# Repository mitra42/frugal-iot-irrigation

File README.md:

# Frugal-IoT Irrigation

This project is intended to provide solar-powered irrigation for small farms. A set of sectors is watered one at a time, once a day. 

The default version waters each sector until its soil reaches a target moisture or a time limit runs out, but it can be 
subclased for more complex per-sector requirements. 

There are tank-level and battery interlocks that stop the whole run, and this also can be customized. 

It is built on top of Frugal-IoT and both the irrigation and MPPT components draw part of their
inspiration from [OSPIT](https://www.apc.org/en/news/meet-ospit-sustainable-energy-and-irrigation-solution-community-networks)
(Lua on the FF-ESP32-OpenMPPT solar charge controller)
- [OSPIT_COMPARISON.md](OSPIT_COMPARISON.md) describes what is different and why.

This release should work in several hardware environments.

* The "FF-ESP32-OpenMPPT solar charge controller" in which case it will run MPPT 
* Our custom boards in `hardware`: an all-in-one irrigation board, or a valve daughter board for the Frugal-IoT sensor board or a plain S2 Mini. 
* A simple off the shelf dev board with hardwired sensors, just edit board definitions in 
  platformio.ini and `wiring` in frugal-iot-irrigation.ino
* A distributed sensor environment, just change the `wiring` in frugal-iot-irrigation.ino 
  to point at the distributed sensors

[Frugal-IoT](https://github.com/mitra42/frugal-iot) brings: WiFi setup from a phone; MQTT; web and phone dashboards; graphing and over-the-air updates.  

Any of the other features of Frugal-IoT can be easily added to your sketch including, off-internet operation, remote sensors, LoRa, or a wide range of other sensors for example for weather. 

## What it does today

- **Up to N irrigation sectors**, run strictly in order, one valve open at a time.
- **Soil moisture per sector** from RS485/Modbus probes sharing one bus, or from simple
  analog capacitive soil sensors.
- Anomaly handling - for instance, a sector whose probe is **not reporting is skipped**
- **Tank level** from a float sender, with two thresholds: one to begin a run, a lower one to
  abort it. "No tank sensor fitted" is kept distinct from "tank empty".
- **Battery interlock** - irrigation stops below a configurable voltage and resumes above a higher
  one.
- Optional **pump** (driven with the valves) and **load output** (e.g. for a router) (switched by the
  battery interlock) on separate pins.
- Optional **OLED**: Displays battery; sector moistures; tank and communicationss status.
- **Solar charge control** - two-stage MPPT tracking with temperature compensation, a hard
  thermal cut-out, and battery-type profiles.
- **Battery reporting** - state of charge and a health estimate inferred from voltage drop.

## Status

**None of the charge control has run on real hardware yet**, so it ships switched off. 

Run the checks in [TESTING.md](TESTING.md) and then turn on `mppt/automatic`

`HARDWARE-QUESTIONS.md` is a list of things we need someone with the OSPIT hardware to
look at and confirm.

## Hardware

Five boards are supported out of the box. See `platformio.ini` for the full pin list, and the wiring
diagrams below for the three you wire up yourself.

| Board | env | Notes |
|---|---|---|
| **FF-ESP32-OpenMPPT** | `ff_openmppt` | the solar charge controller OSPIT runs on. Pin assignments are OSPIT's own |
| **Lolin S2 Mini + irrigation daughter board** | `s2_mini_daughter` | a plain dev board driving `hardware/irrigation-daughter` over I2C |
| **Frugal-IoT Irrigation V0.2** | `frugal_irrigation_v02` | `hardware/irrigation-layout-oct-2026`: eight MOSFET valve outputs, RS485, 12 V buck, LiPo charging, all on one board |
| **Frugal-IoT sensor board V0.2 + irrigation daughter board** | `sensor_v02_daughter` | the [sensor board](https://github.com/mitra42/frugal-iot-hw-sensor) driving the daughter board |
| **Lolin S2 Mini** | `s2_mini` | valves straight from GPIOs, through a driver of your own; no charging hardware |
| other | | Setting up support for most other boards is trivial, look in the [Frugal-IoT/examples/all](https://github.com/mitra42/frugal-iot/blob/main/examples/all/platformio.ini) for example configuration for many popular boards or [add a new issue](https://github.com/mitra42/frugal-iot-irrigation/issues/new) in this repo. |

The **irrigation daughter board** (`hardware/irrigation-daughter`) is the irrigation board's eight valve drivers
on their own: a TCA9534 I2C expander, a MOSFET, flyback diode and LED per valve, a fused and protected 12 V
input, a header for the OLED, and a 12 V battery reading for the host. Paired with the sensor board it costs
about the same as the all-in-one V0.2 board, and the expensive half is a board made in larger numbers. Its host
is powered from 5 V USB - most MPPT charge controllers have a USB port - and its valves from the 12 V battery.

The `FF-ESP32-OpenMPTT` board has the needed functionality, but is going to be a significantly more expensive
solution than the Frugal-IoT boards paired, if neccessary, with an off-the-shelf MPPT controller.

You will also need: 12 V DC valves (not latching, not 24 V AC), one Modbus soil probe per sector, and
optionally a tank float sender and a pump.

The hardware in `hardware` is available as a full set of Gerber and fabrication files, designed for JLCPCB
but could be adapted to any manufacturer (and we would be happy to add files for other manufacturers). Note this
hardware has (as of Nov 2026) yet to be built and tested.

### Sectors and the pump

Every env runs **three sectors and a pump**: valves 1-3 and the pump on the first four outputs. A board with
more outputs - all three below have eight - can run up to seven sectors: uncomment `IRRIGATION_VALVE4_BIT`
(and 5, 6, 7) in its env. Each line adds a valve, a soil probe at the next Modbus slave id (5, 6, ...) and a
sector; the `.ino` picks them up by `#ifdef`. The OLED's soil page shows sectors 1-3 only.

### Wiring

Colours: red power, black ground, green, blue and purple signals. At a valve, blue is the side the board switches
to ground; valves are not polarised, so either lead will do. Each diagram shows the whole system: a solar panel
into an MPPT charge controller, the controller charging the 12 V battery, and the battery feeding the board's
12 V terminal.

**Lolin S2 Mini + daughter board** (`s2_mini_daughter`). The S2 Mini runs from the charge controller's USB
socket. To the daughter board's J1: GND, SDA (GPIO16), SCL (GPIO18), 3V3, and the battery reading V12 to GPIO3.
The daughter board's logic runs from the S2's 3V3, so it is always on. An RS485 module for the soil probes on
GPIO33 (RX, from the module's RO) and GPIO35 (TX, to its DI). It must run from **3.3 V** and switch direction
by itself: a module powered from 5 V puts 5 V on RO, which the S2 cannot take. The I2C pins are 16/18 rather
than the S2's usual 33/35 so that none of these wires cross. The S2 Mini has no I2C pull-ups; the daughter board's
4.7k pull-ups (R19/R20) are fitted for that reason.

**Frugal-IoT Irrigation V0.2** (`frugal_irrigation_v02`). Everything is on the board: valves and pump on
J11-J14, RS485 probes on J10 (which also powers them, from switched 5 V), OLED on J9. The board runs from the 12 V
battery on J2 (its own 5 V converter), so it needs no USB except for programming.

**Frugal-IoT sensor board V0.2 + daughter board** (`sensor_v02_daughter`). The sensor board runs from the charge
controller's USB socket, into its USB-C. A 5-wire cable from its J2 to the daughter board's J1, which reads GND,
SDA, SCL, 3V3, V12 left to right - the sensor board's J2 pins 1, 2, 3, 4 and 9 top to bottom, so the cable runs
straight. The daughter board's logic runs from the sensor board's switched 3.3 V rail: when it is off, every valve
is off. RS485 probes go on the sensor board's J3 (A, B, GND), and take their supply from the 12 V battery - the
sensor board has only 3.3 V there.

The diagrams are generated by `docs/wiring.py`; the three Frugal-IoT boards are KiCad's 3D renders of their
layouts, so they look as assembled and the labels are exactly what is printed on them. The S2 Mini drawing is Peter Van Epp's Fritzing part.

## Building

### PlatformIO (recommended)

```bash
pio run --environment ff_openmppt          # compile
pio run --target upload -e ff_openmppt     # flash
pio run --target uploadfs -e ff_openmppt   # upload data/ (WiFi passwords etc)
pio device monitor -e ff_openmppt          # watch it start
```

The Frugal-IoT library is fetched automatically, so a fresh clone needs nothing set up. 
If you are changing the library at the same time, 
see "Building against a local library" in [CLAUDE.md](CLAUDE.md).

### Arduino IDE

1. **Tools > Manage Libraries**, install **Frugal-IoT**, and choose **Install All** when it asks about dependencies.
2. **Tools > Board > Boards Manager**, and install **esp32** by Espressif Systems.
3. Open `frugal-iot-irrigation.ino` - the whole repository folder is the sketch folder.
4. **Tools > Board**: the row for your hardware below. **Tools > Port**: your board.
5. **Sketch > Show Sketch Folder**, rename `min_spiffs.csv` to `partitions.csv`, and choose
   **Tools > Partition Scheme > No OTA (2MB APP/2MB SPIFFS)** - OTA still works, as `partitions.csv` sets the real layout.
6. **Upload** (→), then **Tools > Serial Monitor** at 115200 baud.

| Tools > Board | configuration |
| --- | --- |
| ESP32 Dev Module | `ff_openmppt` |
| LOLIN S2 Mini | `s2_mini` |
| LOLIN S2 Mini, plus a file `build_opt.h` beside the .ino containing `-DS2_MINI_DAUGHTER` | `s2_mini_daughter` |
| ESP32C3 Dev Module, with **USB CDC On Boot: Enabled** | `sensor_v02_daughter` |
| - | `frugal_irrigation_v02` - PlatformIO only, it uses its own board variant |

`platform.h` is generated from `platformio.ini`. If you change pins there, re-run
`scripts/generate_platform_h.bash`, or the two toolchains will disagree.

### Enrolment secret and debug messages

Optional files, made from the Frugal-IoT library's
[templates](https://github.com/mitra42/frugal-iot/tree/main/templates) - each says how. Never commit them.

* `platformio-secrets-local.ini`, or `platform-secrets-local.h` for Arduino IDE - the enrolment
  secret, so the node joins your organization without an administrator approving it.
* `platformio-local.ini` - debug flags and serial port.

More in [Getting Started](https://github.com/mitra42/frugal-iot/wiki/Getting-Started#next-steps).

## First run

1. Flash, then power up. The device makes its own WiFi network - connect a phone to it.
2. A setup page opens (or browse to `192.168.4.1`). Give it your WiFi name and password.
3. **Irrigation starts switched off.** Turn it on in the **Irrigation** section, and set
   the start time while you are there.

#### FF board testing
We don't have a FF board to try out, so would appreciate feedback. 

`TESTING.md` walks through commissioning a real board step by step, including calibrating the tank and the battery. `HARDWARE-QUESTIONS.md` is a list of things we need someone with the OSPIT hardware to look at.

Because not everyone has sun, a multimeter and a fortnight, `docs/` holds three ready-made plans —
[bench](docs/plan-bench.md), [sunny half-day](docs/plan-sunny-session.md),
[days of running](docs/plan-long-run.md) — each a short ordered list of which Parts of `TESTING.md`
to do. Question 9 of `HARDWARE-QUESTIONS.md` picks one. [docs/sleep-test.md](docs/sleep-test.md) is
the one test that needs its own build, on the `sleep-test` branch.

## Licence

Same as Frugal-IoT. The OSPIT algorithms parts of this are derived from are GPL-2.0-or-later,
Copyright (C) 2026 Corinna 'Elektra' Aichele.

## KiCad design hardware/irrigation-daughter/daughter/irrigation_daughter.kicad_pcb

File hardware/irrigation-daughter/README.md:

# Frugal-IoT Irrigation Daughter V0.1

> **Status (21 Nov 2026): schematic, layout and JLCPCB files done, DRC clean — for review, not yet ordered or
> built.** Decisions D1–D12 in DECISIONS.md.

An add-on that gives a Frugal-IoT **sensor board** (frugal-iot-hw-sensor V0.2) or **LoRa board**
(frugal-iot-hw-lora V0.3) eight 12 V DC valve outputs and an OLED. It is the valve-driver half of the irrigation
board (`../irrigation-layout-oct-2026`) on its own: the host does WiFi/LoRa, charging and sensors; this board
switches valves when the host tells it to over I2C.

## How it fits together

```
 solar panel ─► MPPT charge controller ─► 12 V battery
                   │ USB 5 V                 │ 12 V
                   ▼                         ▼
             host board (sensor/LoRa)    this board, J2 (12V IN)
               J2 ◄── 5-wire cable ──► J1        J4–J11 ─► eight 12 V valves
```

- **Power:** the host from the controller's USB port (so no 5 V buck is needed); the valves from the 12 V
  battery into J2 — 3 A resettable fuse, reverse-polarity diode, 15 V TVS, as the irrigation board.
- **J1 → host J2**, a 5-way screw terminal reading GND, SDA, SCL, 3V3, V12 from left to right (names printed
  beside it): the first four to host J2 pins 1–4, V12 (the battery voltage through a 560k/100k divider) to host
  J2 pin 9 (SENS2), so the host can stop watering on a flat battery. Wiring diagrams are in the firmware's
  README.md at the top of this repository.
- **Logic** (a TCA9534 I2C expander at 0x20, and the OLED) runs from the host's switched 3.3 V sensor rail. When
  the host turns that rail off, every valve turns off.
- **Valves:** eight channels, each a logic-level MOSFET switching the valve's low side, a flyback diode, and a red
  LED that shows when it is on. 12 V DC solenoid valves, ~2 A each, ~3 A in total. Not latching valves, not
  24 V AC valves. Channels 5–8 can be left unfitted.
- **I2C pull-ups:** R19/R20, 4.7k to 3V3, fitted - an S2 Mini host has none of its own. With a sensor or LoRa
  host they sit in parallel with the host's, which is fine (D12).
- **OLED:** J3, a 4-pin header for a 128×64 SSD1306 module (GND, VCC, SCL, SDA), on the same I2C bus.
- **Not here:** RS485 soil probes stay on the host's RS485 terminal; how to power them (most need 5–30 V) is
  open until there is experimental evidence (D1).

Board: 100 × 42 mm, 2 layers, 4 × M3 corner holes; valve terminals along the bottom edge, 12 V on the left, host
and OLED connectors on the top.

## Cost (JLCPCB, Nov 2026)

About **$8.21 per board for 10, $4.46 for 100**, assembled, before shipping. With a sensor board, $19.72 / $11.62
— slightly under the all-in-one irrigation board ($21.04 / $12.07). The bare PCB is estimated, not yet quoted.
Breakdown in COST-ESTIMATE.txt; comparison in DECISIONS D7.

## Points for reviewers

1. The MPPT controller's USB ground must be the battery negative (D9) — check before wiring.
2. Firmware: the irrigation app needs a build for each host board (D10).
3. One I2C address (0x20): two add-ons on one host would need address jumpers (D3).
4. Before ordering: follow *How to order from JLCPCB* in `fabrication/README.md`, including checking part rotations in the assembly preview.

## What's in this folder

| | |
|---|---|
| `SCHEMATIC.pdf` | Schematic, one sheet |
| `PCB-LAYOUT.pdf` | 3D views and both copper layers |
| `BOM.csv` | Bill of materials with LCSC (JLCPCB) part numbers |
| `COST-ESTIMATE.txt` | JLCPCB cost for 10 and 100 boards |
| `DECISIONS.md` | Design decisions and why (D1–D12) |
| `fabrication/` | Files to order from JLCPCB — see its README |
| `daughter/` | KiCad 10 project |
| `claude-tools/` | Scripts Claude uses to regenerate the design — reviewers can ignore |

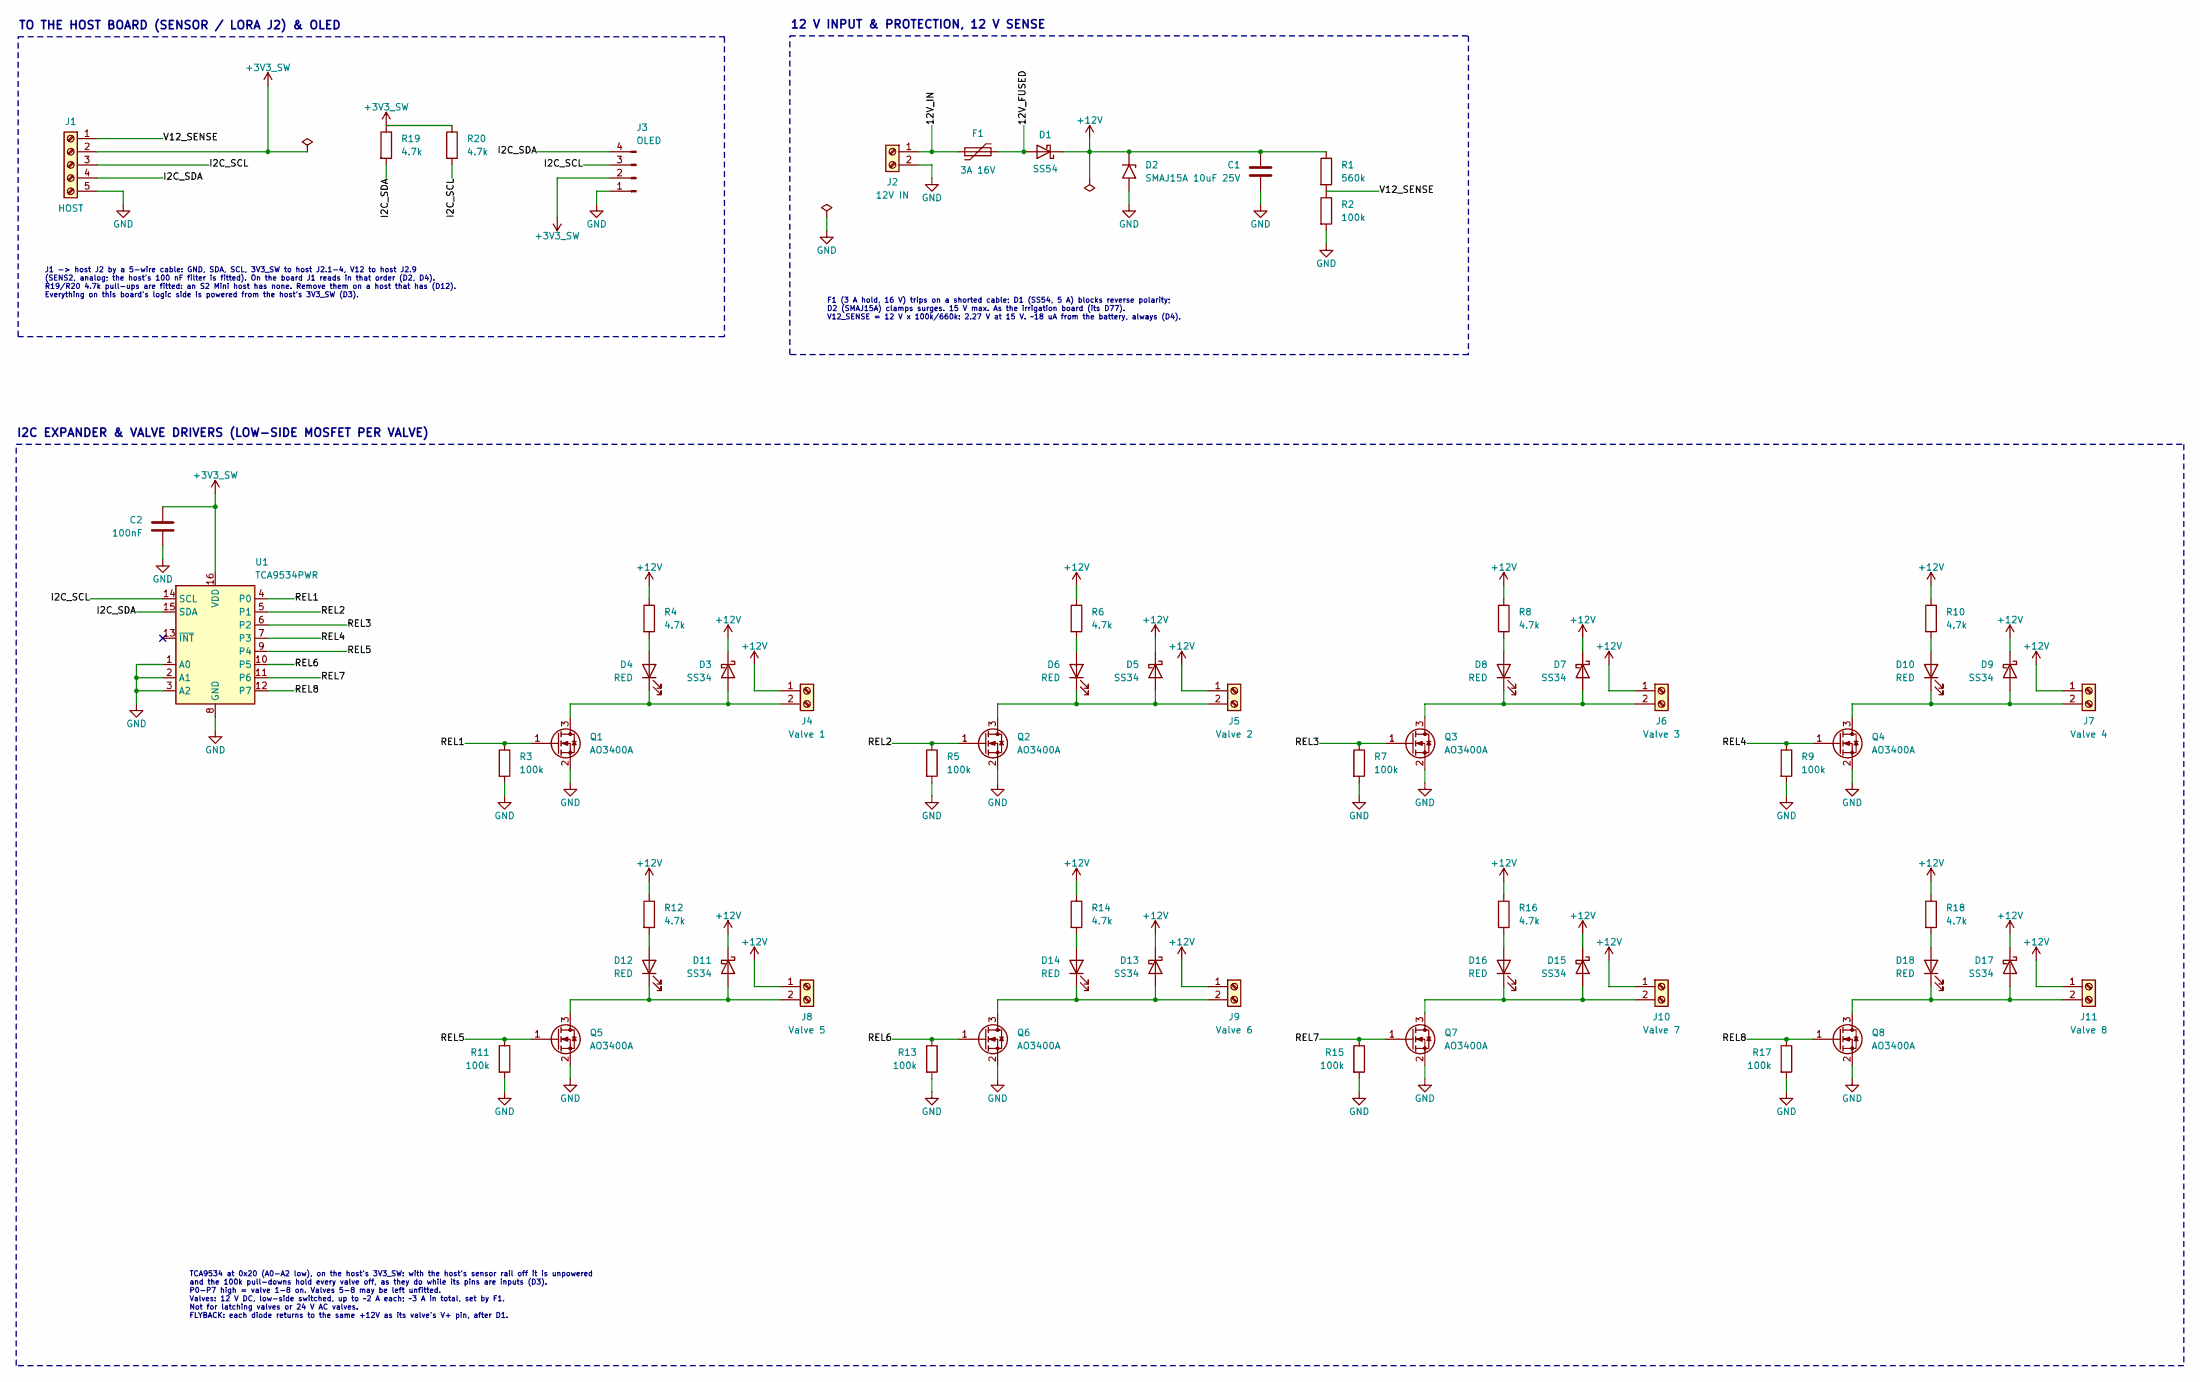
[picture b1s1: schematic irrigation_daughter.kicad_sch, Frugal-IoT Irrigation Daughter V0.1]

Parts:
C1: 10uF 25V; C_1206_3216Metric; MPN 10uF 25V; LCSC C13585
C2: 100nF; C_0603_1608Metric; MPN 100nF; LCSC C14663
D1: SS54; D_SMA; MPN SS54; LCSC C22452
D2: SMAJ15A; D_SMA; MPN SMAJ15A; LCSC C19077535
D3, D5, D7, D9, D11, D13, D15, D17: SS34; D_SMA; MPN SS34; LCSC C8678
D4, D6, D8, D10, D12, D14, D16, D18: RED; LED_0603_1608Metric; MPN KT-0603R; LCSC C2286
F1: 3A 16V; Fuse_1812_4532Metric; MPN SMD1812P300TF/16; LCSC C702820
J1: HOST; TerminalBlock_Xinya_XY308-2.54-5P_1x05_P2.54mm_Horizontal; MPN XY308-2.54-5P; LCSC C915914
J2: 12V IN; TerminalBlock_KF128-5.08-2P; MPN KF128-5.08-2P; LCSC C474952
J3: OLED; PinHeader_1x04_P2.54mm_Vertical; MPN PZ254V-11-04P; LCSC C492403
J4: Valve 1; TerminalBlock_KF128-5.08-2P; MPN KF128-5.08-2P; LCSC C474952
J5: Valve 2; TerminalBlock_KF128-5.08-2P; MPN KF128-5.08-2P; LCSC C474952
J6: Valve 3; TerminalBlock_KF128-5.08-2P; MPN KF128-5.08-2P; LCSC C474952
J7: Valve 4; TerminalBlock_KF128-5.08-2P; MPN KF128-5.08-2P; LCSC C474952
J8: Valve 5; TerminalBlock_KF128-5.08-2P; MPN KF128-5.08-2P; LCSC C474952
J9: Valve 6; TerminalBlock_KF128-5.08-2P; MPN KF128-5.08-2P; LCSC C474952
J10: Valve 7; TerminalBlock_KF128-5.08-2P; MPN KF128-5.08-2P; LCSC C474952
J11: Valve 8; TerminalBlock_KF128-5.08-2P; MPN KF128-5.08-2P; LCSC C474952
Q1, Q2, Q3, Q4, Q5, Q6, Q7, Q8: AO3400A; SOT-23; MPN AO3400A; LCSC C20917
R1: 560k; R_0603_1608Metric; MPN 560k; LCSC C23203
R2, R3, R5, R7, R9, R11, R13, R15, R17: 100k; R_0603_1608Metric; MPN 100k; LCSC C25803
R4, R6, R8, R10, R12, R14, R16, R18, R19, R20: 4.7k; R_0603_1608Metric; MPN 4.7k; LCSC C23162
U1: TCA9534PWR; TSSOP-16_4.4x5mm_P0.65mm; MPN TCA9534PWR; LCSC C783615

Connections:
/12V_FUSED: D1.2 (A), F1.2
/12V_IN: F1.1, J2.1
/I2C_SCL: J1.3, J3.3, R20.2, U1.14 (SCL)
/I2C_SDA: J1.4, J3.4, R19.2, U1.15 (SDA)
/REL1: Q1.1 (G), R3.1, U1.4 (P0)
/REL2: Q2.1 (G), R5.1, U1.5 (P1)
/REL3: Q3.1 (G), R7.1, U1.6 (P2)
/REL4: Q4.1 (G), R9.1, U1.7 (P3)
/REL5: Q5.1 (G), R11.1, U1.9 (P4)
/REL6: Q6.1 (G), R13.1, U1.10 (P5)
/REL7: Q7.1 (G), R15.1, U1.11 (P6)
/REL8: Q8.1 (G), R17.1, U1.12 (P7)
/V12_SENSE: J1.1, R1.2, R2.1
unnamed: D3.2 (A), D4.1 (K), J4.2, Q1.3 (D)
unnamed: D4.2 (A), R4.2
unnamed: D5.2 (A), D6.1 (K), J5.2, Q2.3 (D)
unnamed: D6.2 (A), R6.2
unnamed: D7.2 (A), D8.1 (K), J6.2, Q3.3 (D)
unnamed: D8.2 (A), R8.2
unnamed: D10.2 (A), R10.2
unnamed: D9.2 (A), D10.1 (K), J7.2, Q4.3 (D)
unnamed: D11.2 (A), D12.1 (K), J8.2, Q5.3 (D)
unnamed: D12.2 (A), R12.2
unnamed: D13.2 (A), D14.1 (K), J9.2, Q6.3 (D)
unnamed: D14.2 (A), R14.2
unnamed: D15.2 (A), D16.1 (K), J10.2, Q7.3 (D)
unnamed: D16.2 (A), R16.2
unnamed: D17.2 (A), D18.1 (K), J11.2, Q8.3 (D)
unnamed: D18.2 (A), R18.2

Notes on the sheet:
12 V INPUT & PROTECTION, 12 V SENSE
TCA9534 at 0x20 (A0-A2 low), on the host's 3V3_SW: with the host's sensor rail off it is unpowered and the 100k pull-downs hold every valve off, as they do while its pins are inputs (D3). P0-P7 high = valve 1-8 on. Valves 5-8 may be left unfitted. Valves: 12 V DC, low-side switched, up to ~2 A each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
F1 (3 A hold, 16 V) trips on a shorted cable; D1 (SS54, 5 A) blocks reverse polarity; D2 (SMAJ15A) clamps surges. 15 V max. As the irrigation board (its D77). V12_SENSE = 12 V x 100k/660k: 2.27 V at 15 V. ~18 uA from the battery, always (D4).
I2C EXPANDER & VALVE DRIVERS (LOW-SIDE MOSFET PER VALVE)
J1 -> host J2 by a 5-wire cable: GND, SDA, SCL, 3V3_SW to host J2.1-4, V12 to host J2.9 (SENS2, analog; the host's 100 nF filter is fitted). On the board J1 reads in that order (D2, D4). R19/R20 4.7k pull-ups are fitted: an S2 Mini host has none. Remove them on a host that has (D12). Everything on 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
TO THE HOST BOARD (SENSOR / LORA J2) & OLED

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
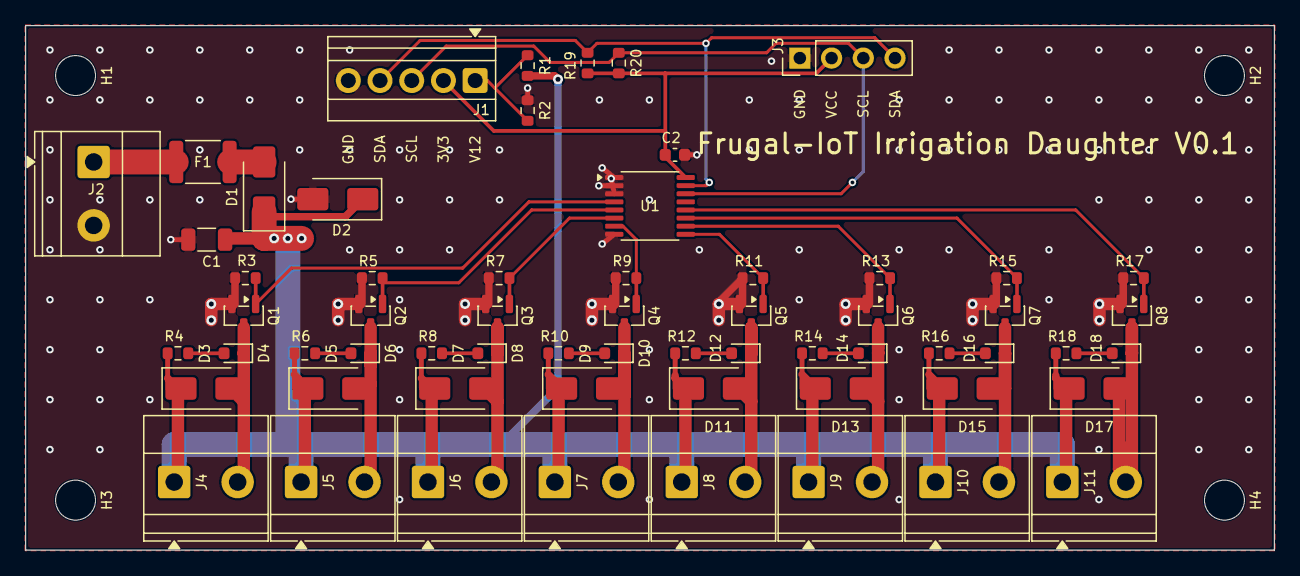
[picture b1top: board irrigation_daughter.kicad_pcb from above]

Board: 2 copper layers, 100.0 x 42.0 mm, 65 parts (0 on the bottom side), 32 nets.

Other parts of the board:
H1, H2, H3, H4: M3; MountingHole_3.2mm_M3

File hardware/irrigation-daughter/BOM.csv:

"Refs","Value","MPN","LCSC","Footprint","Qty","DNP","Note"
"C1","10uF 25V","10uF 25V","C13585","Capacitor_SMD:C_1206_3216Metric","1","",""
"C2","100nF","100nF","C14663","Capacitor_SMD:C_0603_1608Metric","1","",""
"D1","SS54","SS54","C22452","Diode_SMD:D_SMA","1","",""
"D2","SMAJ15A","SMAJ15A","C19077535","Diode_SMD:D_SMA","1","",""
"D3,D5,D7,D9,D11,D13,D15,D17","SS34","SS34","C8678","Diode_SMD:D_SMA","8","",""
"D4,D6,D8,D10,D12,D14,D16,D18","RED","KT-0603R","C2286","LED_SMD:LED_0603_1608Metric","8","",""
"F1","3A 16V","SMD1812P300TF/16","C702820","Fuse:Fuse_1812_4532Metric","1","",""
"J1","HOST","XY308-2.54-5P","C915914","TerminalBlock:TerminalBlock_Xinya_XY308-2.54-5P_1x05_P2.54mm_Horizontal","1","",""
"J2","12V IN","KF128-5.08-2P","C474952","irrigation:TerminalBlock_KF128-5.08-2P","1","",""
"J3","OLED","PZ254V-11-04P","C492403","Connector_PinHeader_2.54mm:PinHeader_1x04_P2.54mm_Vertical","1","",""
"J4","Valve 1","KF128-5.08-2P","C474952","irrigation:TerminalBlock_KF128-5.08-2P","1","",""
"J5","Valve 2","KF128-5.08-2P","C474952","irrigation:TerminalBlock_KF128-5.08-2P","1","",""
"J6","Valve 3","KF128-5.08-2P","C474952","irrigation:TerminalBlock_KF128-5.08-2P","1","",""
"J7","Valve 4","KF128-5.08-2P","C474952","irrigation:TerminalBlock_KF128-5.08-2P","1","",""
"J8","Valve 5","KF128-5.08-2P","C474952","irrigation:TerminalBlock_KF128-5.08-2P","1","",""
"J9","Valve 6","KF128-5.08-2P","C474952","irrigation:TerminalBlock_KF128-5.08-2P","1","",""
"J10","Valve 7","KF128-5.08-2P","C474952","irrigation:TerminalBlock_KF128-5.08-2P","1","",""
"J11","Valve 8","KF128-5.08-2P","C474952","irrigation:TerminalBlock_KF128-5.08-2P","1","",""
"Q1-Q8","AO3400A","AO3400A","C20917","Package_TO_SOT_SMD:SOT-23","8","",""
"R1","560k","560k","C23203","Resistor_SMD:R_0603_1608Metric","1","",""
"R2,R3,R5,R7,R9,R11,R13,R15,R17","100k","100k","C25803","Resistor_SMD:R_0603_1608Metric","9","","valve off at reset"
"R4,R6,R8,R10,R12,R14,R16,R18-R20","4.7k","4.7k","C23162","Resistor_SMD:R_0603_1608Metric","10","","I2C pull-up; remove if the host has its own"
"U1","TCA9534PWR","TCA9534PWR","C783615","Package_SO:TSSOP-16_4.4x5mm_P0.65mm","1","",""
